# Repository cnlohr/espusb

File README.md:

# ESP8266 USB Software Driver

I wanted to have USB on the ESP8266, and a while ago I saw on the ESP32 flier, it read: "Rich Peripherals" ... "Sorry, no USB!" I thought to myself, that is ridiculous.  Of course there's USB.

So, it was born.  This is a software USB stack running on the ESP8266/ESP8285.  It requires only one external resistor, between D- and 3.3V.

## Limitations

- You cannot use SDKs newer than 1.5.X. (As of dec-02-2016, 1.5.4 is the latest SDK that has been verified to be compatible.)
- All ESP SDK 2.0 SDKs are incompatible.
- By default, the chip expects D- on GPIO 4 and D+ on GPIO 5 - but any GPIO pair may be used.  It is important to note that both D- and D+ MUST be adjacent.
- This project only operates with low-speed USB (1.5 MBit/s)
  ideal for making peripherals, not for fake network devices and usb-serial bridges.  
  That said - you can still write "control" messages that communicate with the ESP8266.  
  Control messages are a great way to encapsulate your data since they handle all the framing and describing what function you wish to pass data for.

## Resources
- [Getting started guide](https://github.com/cnlohr/espusb/wiki/Getting-Started-Guide)
- [Forum for discussion of development](http://www.esp8266.com/espusb)

## Pre-built binaries

See bottom of this thread: https://github.com/cnlohr/espusb/issues/40#issuecomment-377770936

## Examples

This project contains an example that simulates a usb keyboard and mouse. It also provides a web interface to actually remote control these virtual devices.

## How to use
For a complete guide that includes information on how to install the toolchain or set up a docker container, go here: [Getting started guide](https://github.com/cnlohr/espusb/wiki/Getting-Started-Guide)
If you already have an environment with the toolchain, then here is what you wanna do:

### Software

- Install libusb and recursively clone this repo: 
  
  ``` bash
  sudo apt-get install libusb-1.0-0-dev
  git clone --recursive https://github.com/cnlohr/espusb
  cd espusb
  ```

- `user.cfg` contains some settings that you might have to change to get it working. 

- Building/flashing the main binary
  
  ``` bash
  make ESP_ROOT=~/esp8266/esp-open-sdk/ burn
  ```

- Building/flashing the web interface (for the example mentioned above)
  
  ``` bash
  make ESP_ROOT=~/esp8266/esp-open-sdk/ burnweb
  ```

For more advanced building/flashing methods just run `make` without any parameters.

### Hardware

### Wemos D1 Mini

The Wemos D1 mini is a breadboard friendly ESP board.

You would need to flash the espusb firmware through the USB-serial connection beforehand, and then
wire the GND, 5V, 3.3V, D1, D2 pins to the USB following the wiring instructions. Here is
a picture of a setup with one breadboard:

## Advanced information

### Hardware

NOTE: GPIO12/14 do not need to be connected to ground. GPIO15 may be connected via a pull-down resistor.  For stability, a pull-up on GPIO2 is recommended.

Also, checkout the hardware/ folder.  It has kicad designs for my tiny board.  Though they are for the ESP8285, the same pin configuration may be used to run on the ESP8266.

### Memory Usage

This is typical memory usage for a two-endpoint (in addition to EP0) device.

In summary:

Total SRAM: 232 bytes + Descriptors (~317 bytes)

Total Flash/IRAM (Only iram, tables and usb_init can be stuck in slow flash): 1422 bytes

More details:

SRAM:

```
0000007c D usb_ramtable
0000006c B usb_internal_state
```
IRAM:

You must write: usb_handle_custom_control - the demos here hook it up to the command engine which allows self flashing on 1MB+ parts.

C functions:
```
0000002a T usb_pid_handle_ack
0000014f T usb_pid_handle_data
00000022 T usb_pid_handle_out
000000e9 T usb_pid_handle_in
00000002 T usb_pid_handle_sof
00000039 T usb_pid_handle_setup
```
From/To (in ASM):
```
40100f20 t usb_asm_start
401011ef t usb_asm_end
Total length of ASM: 2cf
```

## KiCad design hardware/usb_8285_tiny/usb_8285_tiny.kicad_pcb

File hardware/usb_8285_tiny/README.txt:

Someone said it worked.  So, I think this works?

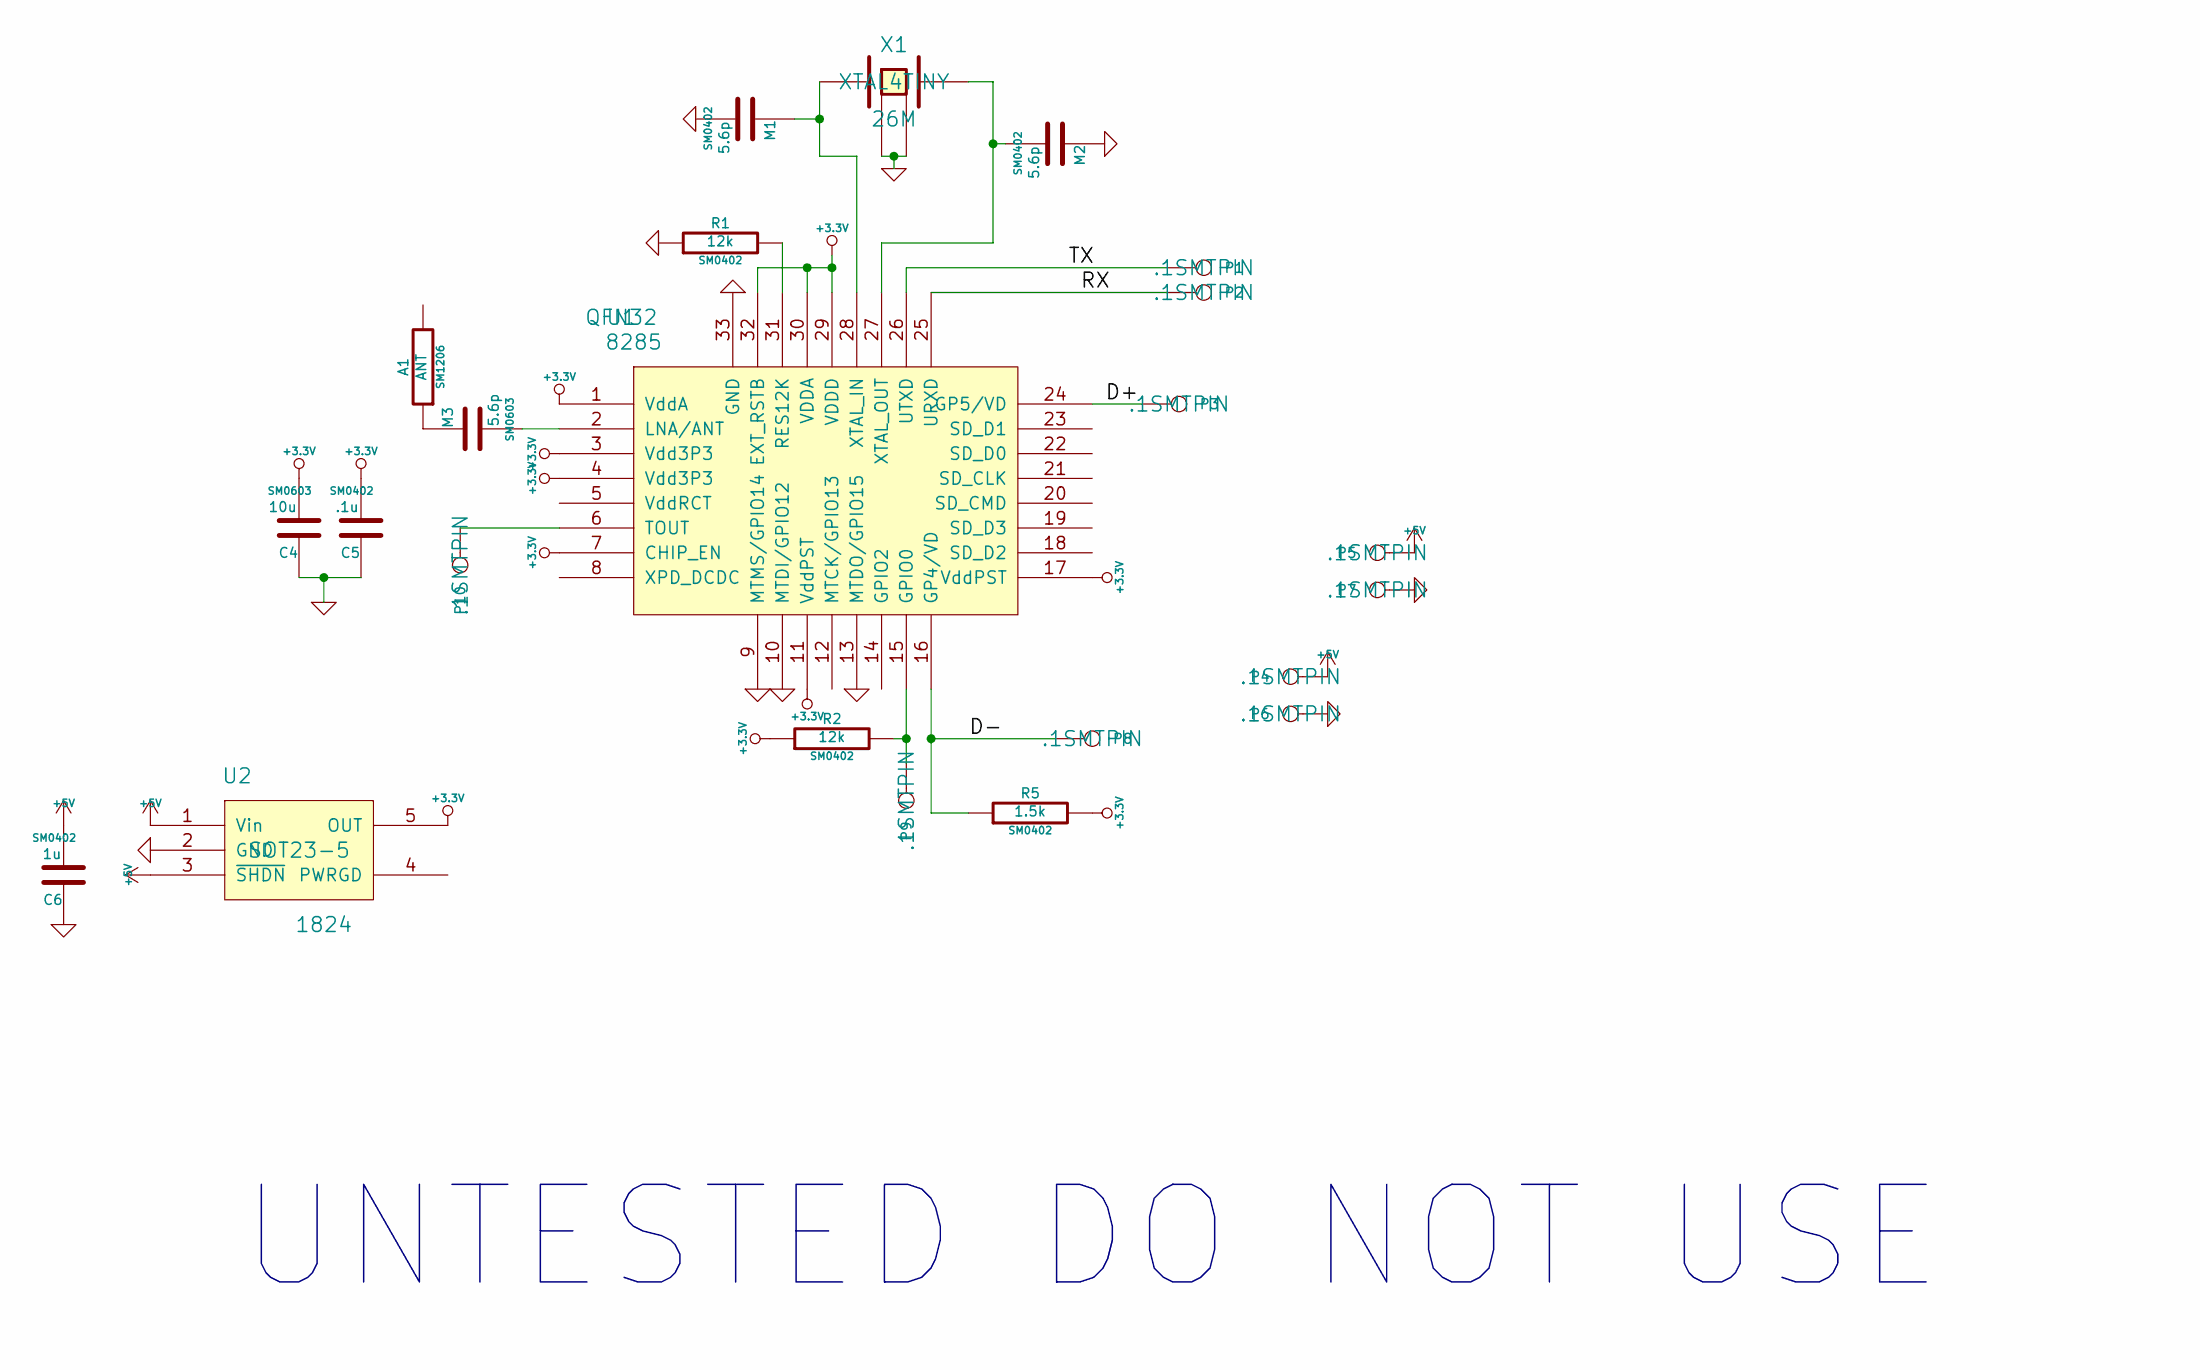
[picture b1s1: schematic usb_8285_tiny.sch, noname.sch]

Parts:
A1: ANT; SM1206; Digikey 1292-1035-1-ND
C4: 10u; SM0603
C5: .1u; SM0402
C6: 1u; SM0402
M1, M2: 5.6p; SM0402
M3: 5.6p; SM0603
P1: UTX; .1SMTPIN
P2: URX; .1SMTPIN
P3: D+; .1SMTPIN
P4, P5: +5V; .1SMTPIN
P6, P7: GND; .1SMTPIN
P8: D-; .1SMTPIN
P9: G0; .1SMTPIN
P10: ADC; .1SMTPIN
R1, R2: 12k; SM0402
R5: 1.5k; SM0402
U1: 8285; QFN32
U2: 1824; SOT23-5
X1: 26M; XTAL4TINY

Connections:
+3.3V: C4.2, C5.2, R2.1, R5.2, U1.1 (VddA), U1.3 (Vdd3P3), U1.4 (Vdd3P3), U1.7 (CHIP_EN), U1.11 (VddPST), U1.17 (VddPST), U1.29 (VDDD), U1.30 (VDDA), U1.32 (EXT_RSTB), U2.5 (OUT)
+5V: C6.2, P4.1, P5.1, U2.1 (Vin), U2.3 (~SHDN)
/D+: P3.1, U1.24 (GP5/VD)
/D-: P8.1, R5.1, U1.16 (GP4/VD)
/RX: P2.1, U1.25 (URXD)
/TX: P1.1, U1.26 (UTXD)
GND: C4.1, C5.1, C6.1, M1.2, M2.1, P6.1, P7.1, R1.1, U1.9 (MTMS/GPIO14), U1.10 (MTDI/GPIO12), U1.13 (MTDO/GPIO15), U1.33 (GND), U2.2 (GND), X1.3 (GND), X1.4 (GND)
unnamed: A1.1, M3.1
unnamed: M1.1, U1.28 (XTAL_IN), X1.1
unnamed: M2.2, U1.27 (XTAL_OUT), X1.2
unnamed: M3.2, U1.2 (LNA/ANT)
unnamed: P9.1, R2.2, U1.15 (GPIO0)
unnamed: P10.1, U1.6 (TOUT)
unnamed: R1.2, U1.31 (RES12K)

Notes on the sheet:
UNTESTED DO NOT USE

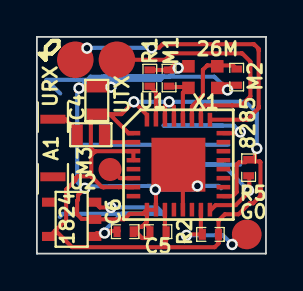
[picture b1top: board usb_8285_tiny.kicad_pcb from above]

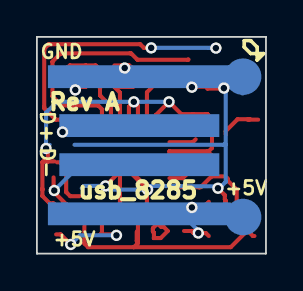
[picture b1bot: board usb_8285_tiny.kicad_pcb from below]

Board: 2 copper layers, 12.7 x 12.0 mm, 23 parts (6 on the bottom side), 14 nets.

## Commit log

2016-08-07 initial commit - does not yet work
2016-08-07 It's a mouse!
2016-08-07 further progress ... still not able to flash due to CRC problems.
2016-08-07 Now accepting flashing through USB!
2016-08-08 a little bit of cleaning up... I still wish I knew why I can't get two HID interrupt endpoints working.
2016-08-10 Add Schematic updates. Add a ton of comments in the ASM, optimize more for size, since speed on usb 1.1 low speed is sufficient.
2016-08-10 Re-work higher-level USB subsystem to treat endpoints uniquely.
2016-08-16 update design to what I actually ordered
2016-08-17 Cleanup - and fix usbflashing
2016-08-18 Major code cleanup. Remove a lot of unneeded stuff
2016-08-18 Update readme and files
2016-08-18 fix # of bytes in descriptors
2016-08-19 Update gitmodules with the esp82xx project
2016-08-19 Update gitmodules
2016-08-19 Switch everything over to esp82xx
2016-08-19 Forgot to add user.cfg
2016-08-19 update repo
2016-08-19 Bump submodule, add make init_submodule
2016-08-20 Specify the SDK I am using, though others probably work.
    Also, update to newer esp82xx, fixes #6
2016-08-20 Fix USB endpoint data subset.
    On many systems, the USB took a long time to enumerate because we were replying with a 'nak' when we were finished sending a descriptor. This is wrong. When a descriptor or control transfer is comple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
    Why doesn't anyone document this stuff well?
2016-08-20 It's OK to send NAKs on control endpoints
2016-08-20 Speed up interval now that everything works right.
2016-08-20 Update for having web-based mouse-click.
2016-08-20 Update with everything from livestream so far.
2016-08-21 Update to something that actually handles keyboard input (Though it is limited)
2016-08-21 Tweak submods. Update Makefile
2016-08-21 Add debugging for when things go badly and need to reboot. Change logic around for the _IN packets.
2016-08-21 Rework Keyboard code.
2016-08-22 refs #7 - Make keyboard better. If only we could figure out why it automatically capitolizes the first letter
2016-08-22 Update to newest esp82xx. Switches to 'esp82xx' from 'mystuff'
2016-08-23 update to newest esp82xx
2016-08-23 Update to newest esp82xx, also change inclusion order to allow user to override parameters.
2016-08-24 Add significant functionality to usb keyboard.
2016-08-27 update hardware - yes, it works!
2016-08-27 Update all, now with a rough draft of a new design
2016-08-27 add schematic
2016-08-27 add readme
2016-08-27 Update iwth notes
2016-08-27 Bumped submodule version
2016-08-27 update webpage
2016-08-27 updated project file for schematics.
2016-08-27 fix layout
2016-08-27 remove unneeded files
2016-08-30 bumped submodule
2016-08-31 add tiny
2016-08-31 forgot to remove the rpt's
2016-08-31 Switch to ESP8285, update webpage to use password. Clear debug screen on reboot.
2016-09-04 Tweak designs, update user config, etc. to work nicely with new esp82xx project, remove debug pin (for now), speed up tick time some.
2016-09-04 bmp submodule
2016-09-04 Fix name of project, use ESP8266, but, this is mostly irrelevant now once first programmed. Also bump submodule.
2016-09-04 bumpt submodule
2016-10-08 Make USB play better with subprojects, and allow much larger custom control messages.
2016-10-08 Update with USB bootloader!
2016-10-08 add a binary
2016-10-08 Cleanup - separate out send/receive buffers.
2016-10-08 Make bootloader smarter, able to handle control messages.
2016-10-08 Update documentation in main
2016-10-17 Cleanup use of ws2812's
2016-12-02 major readme improvements
2016-12-02 web interface now uses bootstrap (not finished yet)
2016-12-03 Revert "web interface now uses bootstrap (not finished yet)"
    This reverts commit e3f2b92025351c0ae92c5e51e8d382b304f82d67.
2017-01-13 add Wemos D1 mini example
2017-01-13 Revert "add Wemos D1 mini example"
2017-01-14 add a better picture of the wemos setup, fix the wires used
2017-01-14 Update README.md
    Typo for the word "connection" and reword the first paragraph
2017-01-17 Add fullspeed test to fstest.
2017-10-29 allow non-adjacent DM/DP-pins
    Allow DPLUS and DMINUS to be set to non-adjacent pins. This incurs some
    additional delay in the USB loop, but it still seems to be within
    limits.
2018-02-17 add page.mpfs to help people who just want to use it.
2018-04-01 added german keyboard layout
2018-06-10 Added "Tab" to special keys list
2022-09-08 Galeri
    Photo video
